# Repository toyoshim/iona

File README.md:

# Tested

The code was tested on a prototype board by Stefano Minozzi (cyllboy).

Freel free to contact for questions about code and board.

# IONA - JVS IO Board by Arduino Pro Micro

Original code by [Takashi Toyoshima](https://github.com/toyoshim).

This program makes an Arduino Pro Micro (With atmega 32u4) work as a JVS IO Board that allows you to connect a legacy JAMMA joystick to a JVS based arcade system, such as NAOMI.

Since now underlying [jvsio](https://github.com/toyoshim/jvsio) library supports several boards and devices, you would be able to run this on other boards with minimal hacks.

Also there is [another example](https://github.com/toyoshim/iona-js) to run iona compatible functionalities without the Arduino firmware.

## Schematic

This program makes an Arduino Pro Micro work as a JVS IO Board that allows youto connect a legacy AES compatible joystick gamepad (included Button 5 and 6 for customomized arcade sticks.

Since now underlying [jvsio](https://github.com/toyoshim/jvsio) library supports several boards and devices, you would be able to run this on other boards with minimal hacks.

Also there is [another example](https://github.com/toyoshim/iona-js) to run iona compatible functionalities without the Arduino firmware.

Resistor (R1) and capacitor (C1) are 100Ohm and 100nF 0603 SMD.

The PCB is based in this DB15 AES compatible pinout:
```
.----------------------------------------------------------------.
\ 1:GND   2:B6    3:CDT   4:B4    5:B2    6:RGH   7:DWN   8:+5V  /
 \                                                              /
  \  9:NC   10:B5   11:STR    12:B3   13:B1   14:LFT    15:UP  /
    `---------------------------------------------------------´
```
The Board  has a jumper, if it's shorted then it works as a USB Stick for a computer, using the micro USB of Arduino., else it works aas a JVS for the naomi using the USB B connector.

In JVS mode, the Naomi's USB doesn't give power to the board, use the micro USB connector or the power jumpers on the board (See legend on the back side of the PCB). You can get 5V from CN7 on the Naomi Board.
```
 _________________
| 5V  5V  GND GND |   CN7
 ¯¯¯¯¯¯¯¯¯¯¯¯¯¯¯¯¯
```
## Board (PCB)

## !! Use an Arduino Pro Micro with micro USB connector, the mini USB version is a little wider) !! ##

Note: JVS uses the USB connector, but it isn't the real USB at all.
The protocol is completely different, and it does not provide the 5V power.

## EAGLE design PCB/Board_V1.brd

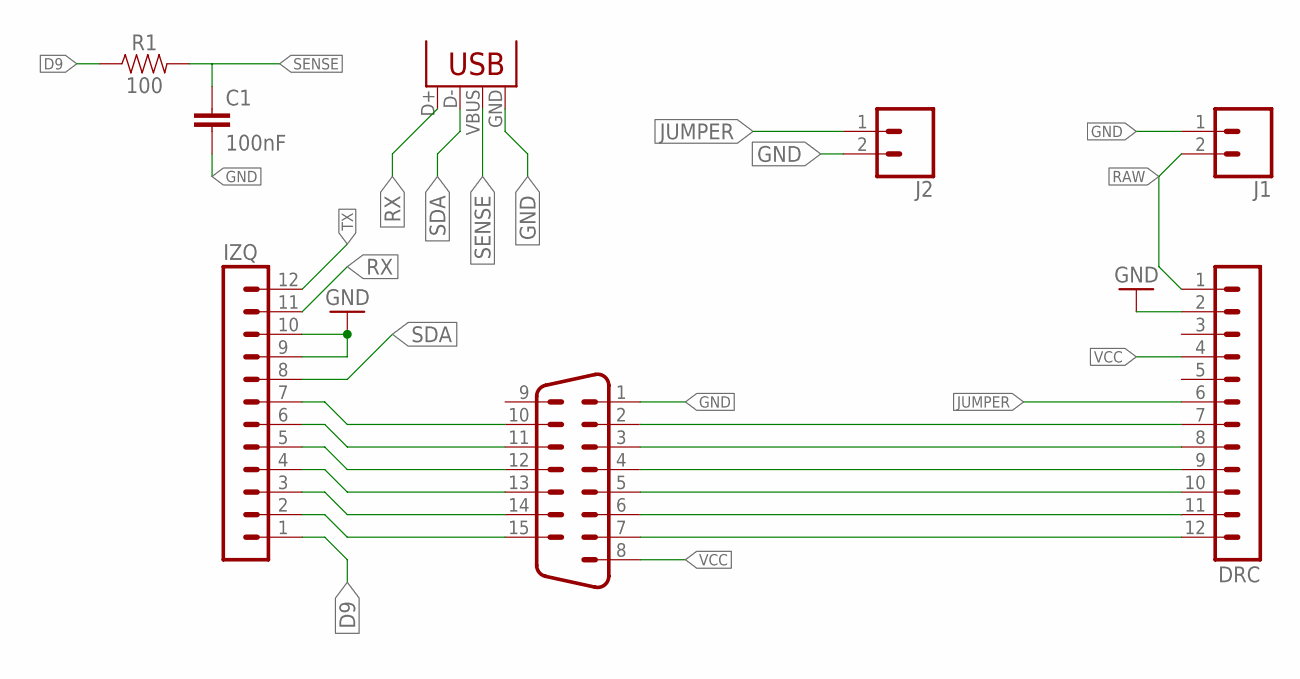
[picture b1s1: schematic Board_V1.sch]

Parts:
C1: 100nF; 0603
DRC: MA12-1
IZQ: MA12-1
J1, J2: CONN_02; 1X02
R1: 100; 0603
X2: USB-B-H
X3: M15V

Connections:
BTN2: DRC.10, X3.5
BTN4: DRC.9, X3.4
BTN6: DRC.7, X3.2
CRD: DRC.8, X3.3
D9: IZQ.1, R1.1
DWN: DRC.12, X3.7
GND: C1.2, DRC.2, IZQ.9, IZQ.10, J1.1, J2.2, X2.GND, X3.1
JUMPER: DRC.6, J2.1
unnamed: IZQ.7, X3.10
unnamed: IZQ.6, X3.11
unnamed: IZQ.5, X3.12
unnamed: IZQ.4, X3.13
unnamed: IZQ.3, X3.14
unnamed: IZQ.2, X3.15
RAW: DRC.1, J1.2
RGH: DRC.11, X3.6
RX: IZQ.11, X2.D+
SDA: IZQ.8, X2.D-
SENSE: C1.1, R1.2, X2.VBUS
TX: IZQ.12
VCC: DRC.4, X3.8

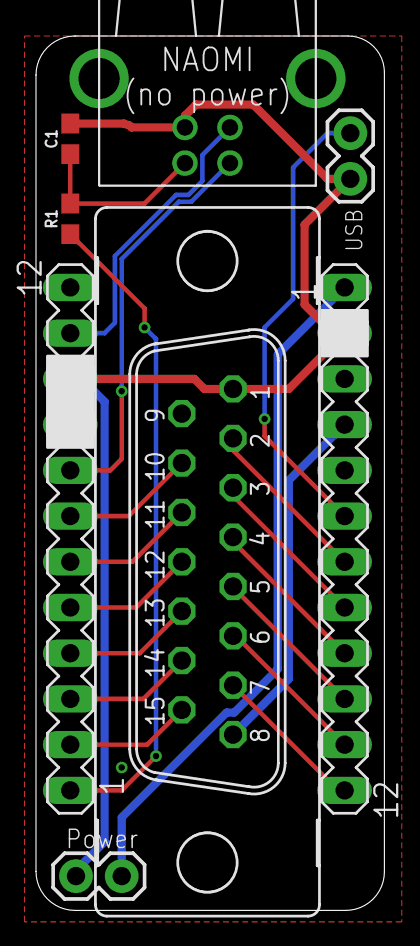
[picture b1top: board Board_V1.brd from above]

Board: 2 copper layers, 19.4 x 48.6 mm, 8 parts (0 on the bottom side), 20 nets.

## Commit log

2018-02-11 Update README.md
    Fix broken layout of schematic.
2018-02-21 coint counter bug fix
2018-02-21 add general purpose output port support to JVSIO
2018-02-22 Su Chi Pai III mode
    Maybe Naomi's common protocol to support mahjong controllers.
    JVS 3 defines an input swith layout for mahjong games, but
    Su Chi Pai use a different protocol, probably because the spec
    hasn't defined yet when the game is launched.
    It uses general purpose output driver to select a input switches
    set to multiplex input switches in the first line .
2018-03-09 Support more naomi games
    To support more naomi games,
    - Use SEGA compatible names for the board ID
    - Change capability to say supporting two players (just saying)
    - Ditto, supporting analog inputs
2018-09-04 Add Virtual-On mode
    Implement Virtual-On mode that emulates the twin stick controller
    by single arcade controller that has only one 1 stick and 4 buttons.
    The arcade stick affects both left and right sticks, but if button 2
    is pressed, right results in turning left, left does turning right,
    up does jumping, and down does cancelling it. Button 1 is L shot,
    button 4 is R shot, and button 3 is turbo for both L and R.
2018-09-07 Split JVSIO library part to a separate submodule
2018-11-21 Update README.md
    5V from JAMMA should be provided via Nano 5V pin.
    VIN needs 7+V for driving regulator to generate expected 5V.
    Probably, JAMMA's 12V may work with VIN, but I haven't tried.
2019-06-02 JVSIO roll
2019-06-09 Bug fix
    - Roll the latest jvsio that fixed bugs
    - Update .ino so to follow the new interface
    Following revisions after recent JVSIO rools haven't worked.
    - 79592a636e6a663a153fc996fef43db999d215f2
    - 228c5826017673b9b91f06f56172fd73c64edcdd
    - 4b75ca0874f5b624ef2a536449ba0e3bdd572fe7
2019-07-21 Coin unit number should start from 1 rather than 0
2019-07-31 CoinSub bug fix: Unit ID should start from 0
2019-08-16 SNES signal polarity fix
    @AtariSTFan confirms it works.
    https://twitter.com/AtariSTFan/status/1157313673444102144
2019-08-16 Experimental implementation to support dual SNES controllers
2019-09-28 Add files via upload
    Code adapted to the PCB
2019-09-28 Rename Placa V1.brd to PCB/Board_V1.brd
2019-09-28 Rename Placa V1.sch to PCB/Board_V1.sch
2019-09-28 Add files via upload
    Minor changes on GND layer
2019-09-28 Add files via upload
    Changed pins for the new board (old one was based on the proto board)
2019-09-28 Add files via upload
    Added info about changes on the code at the header.
2019-09-28 Add files via upload
    Added USB Stick suport for pc/linux/mac.
    Untested
2019-10-29 Update README.md
    Add missed Rs for DIPSWs pull-down
2019-10-29 Update README.md
    Add minimum information to support multiple nodes
2019-10-29 Update credit handling so that it can support tricky titles
2019-10-29 Update credit handling to support more titles
    - Some titles call kCmdIoId on each frame, and it resets the credit
    in the previous code. It should be reset on kCmdReset.
    - Some titles call kCmdCoinSub with a zero origin index, though the
    spec requires it starts with 1. So, we do not check the index to
    support both cases in an easy way.
2019-10-30 It seems some unofficial title expect the function reports are placed in a specific order, such as sw input comes first, then coin input follows, etc.
    Such titles compile a command series to query inputs
    as in the same order as it they appear in the report,
    then fail to parse the coin input coming later.
2019-10-30 README.md cleanup
2019-10-30 backport of the coin fix for unofficial titles
2019-10-30 2P coin support
2019-10-31 bug fix on the coin report, introduced by the 2P credit support
2020-01-15 Expeimental code to support 2P on MegaClient
2020-01-17 Bug fix for SUPPORT_2P
2020-01-17 jvsio roll
    including a refactoring, and haven't checked well with iona :/
2020-01-17 Another fix to support 2P, sending back input data correctly
2020-04-09 Example code to handle analog inputs over analogRead(). You should not call analogRead() in the switch statement since it takes too long time and it violates JVS timing regulation.
2020-08-14 Fix a regression bug introduced in the last submit
    This change fixes the issue 7.
2020-08-16 fix a buffer overrun issue
2020-08-16 use C++11 loop instead of an old school style
2020-12-09 Bug fix and refactoring to support Arduino MEGA correctly
    There is a bug that a wrong pin is assigned for the JVS sense
    on Arduino MEGA. The bug was fixed in jvsio library, and this
    commit contains the jvsio library roll, and iona.ino side fix
    to avoid using the conflicted pin for the SENSE.
    As clean-up, this patch move the pins array to the global space
    and use the definition to scan button inputs.
2021-11-14 Format fix for player 2's first data
2021-11-14 Fix mega2560 2 player support
    - use D2 and D3 instead of D22 and D23 that don't actually exist.

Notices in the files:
parts and their libraries:
SparkFun-Connectors: Licensing: Creative Commons ShareAlike 4.0 International - https://creativecommons.org/licenses/by-sa/4.0
